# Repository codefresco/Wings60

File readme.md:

# Wings60

Wings60 is an open source split keyboard designed after trying many existing split layouts.

## Why this layout

This keyboard is different in:

- Improved key access for the thumb cluster, two 1.5u key with good access.
- Uses a natural thumb cluster orientation selected after testing many existing layouts.
- Uses the most popular column stagger.
- Keeps the same PCB usable for wired or wireless builds, including a power slide switch, JST PH2.0 battery plug, and between-halves interconnects on the PCB.
- Uses USB-C for wired interconnect between halves, it can be hot-plugged without damaging microcontrollers.
- Supports pro-micro pinout controllers such as Nice!Nano, Pro Micro ATmega32u4, and Pro Micro RP2040.
- Uses low-power RGB LEDs (SK6803 mini-e), which draw less power than common WS2812B and SK6812 variants.
- Includes a slide switch to cut LED power for zero LED idle current in power-conscious assemblies.
- Stays compact while keeping a top number row.

## How to assemble

> [!WARNING]
> If you use a 3V microcontroller (for example Nice!Nano or RP2040), do not plug a powered USB cable into the between-halves interconnect USB-C port. With a standard usb c cable and device, this would not be an issue bacause the CC pin on the interconnect is not connected. With a floating CC pin the device would not power the USB-C port. However, some USB-A to USB-C cables or devices do not comply with this standard and present 5v to the USB-C VBUS anyway, and this can damage the microcontroller. To make it mistake proof:
> - For nice! nano compatible and wireless builds print the case with interconect port covered
> - For wired builds with 3V microcontrollers do not connect he VCC pin on microcontroller to the pcb (don't pin if using mill max or similar pins, clip the pin if using ez solder, etc.) and bridge the VCC pin of the PCB to RAW using a short wire on back of the PCB

> [!WARNING]
> Before soldering switches, make sure the microcontroller USB connector is clearly accessible in your chosen case. After switches are soldered, the case top is sandwiched between switches and PCB, and changing the top case becomes difficult. If you want to be able to remove the PCB more easily, check the PCB-mount-switches case variant in [case](./case).

### Bill of materials

- See designs in [case](./case), pick one and print it. You can also design your own case around the [Case design outline](./case/design-outline), both dxf and svg are included.
- Sockets for MCU: one of EZ-Solder Machine Sockets or a 40-pin machined IC breakable female header strip with Mill-Max pins is recommended for a total socket height of 4.5-5mm. This works best with the 3D printable case designs in [case](./case). Check USB connector height after assembly against the case USB opening. If your USB sits higher/lower, use the adjustable USB case variant described in [case/readme.md](./case/readme.md). A good guide to socketing microcontrollers is available here: [Machine pin socket guide](https://github.com/joric/nrfmicro/wiki/Sockets#machine-pin-socket)
- Two pro micros: use any board with firmware already available in [firmware](./firmware), or any pro-micro-pinout compatible board and adjust firmware as needed. For wireless, use Nice!Nano or compatible SuperMini nRF52840.
- Either 4x 9-10mm standoffs with 4x M2x8 and 4x M2x4 screws for each half, or 4x M2x4 heat inserts with the heat-insert-compatible case bottom. See [case/readme.md](./case/readme.md).
- Non-slip rubber feet, 4x per half. 6mm diameter x 2mm height works well.
- [Wired only] A USB-C to USB-C cable for connecting the right and left halves.
- [Wireless only] A JST PH2.0 battery up to 5mm height. Check dimensions against the case if using the designs in [case](./case).
- Switches and keycaps.

### Wired build

1. Flash firmware using instructions here [firmware/readme.md](./firmware/readme.md)
2. Solder and socket the microcontrollers to PCBs, **face down**. USB side must face the PCB. A good socketing guide: [Splitkb microcontroller guide](https://docs.splitkb.com/product-guides/aurora-series/build-guide/microcontrollers)
3. Check USB height to make sure it fits the case designs in [case](./case). If it fits fixed-USB, use that variant; otherwise adjust USB height in the movable/adjustable variant in your slicer.
4. Fit switches to the case, minding pin orientation.

5. Fit the PCB to the case with flat side toward switches and components facing away from switches, so switch pins come out through the PCB. PCB should rest on the bottom of the switches. You may need gentle pressure for switch mounting pins to pop in.
6. Check no switch has popped out, and all switches are firmly seated on top of the case top side. Then solder all switch legs to the PCB.
7. If using standoff bottoms, screw each standoff to the case with M2x8 screws. V-shaped heads sit flush in the top-side recesses.
8. Screw case bottoms to standoffs using M2x4 screws, then apply non-slip feet.
9. If using heat-insert bottoms, install heat inserts and fit the bottom to the top using M4x8 screws.

The halves can now be connected using the USB-C cable. Connect one microcontroller to your PC (either half, but not both).

Use [Vial](https://get.vial.today/) to configure the keyboard. Configuration is saved to the half connected to the PC.

### Wireless build

TBD

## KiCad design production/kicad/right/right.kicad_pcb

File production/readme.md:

## Production Files

You can order this split keyboard from any major PCB manufacturer using the production-ready files in this directory.

- `left/` contains manufacturing files for the left PCB
- `right/` contains manufacturing files for the right PCB

## Example: Ordering from JLCPCB

1. Open JLCPCB and start a new PCB order.
2. Upload the left and right Gerber ZIPs separately (one order per side).
3. Confirm board specs (dimensions, thickness, copper weight, solder mask color, and finish).
4. Keep defaults unless you need specific changes.
5. Add both boards to cart, review, and place the order.

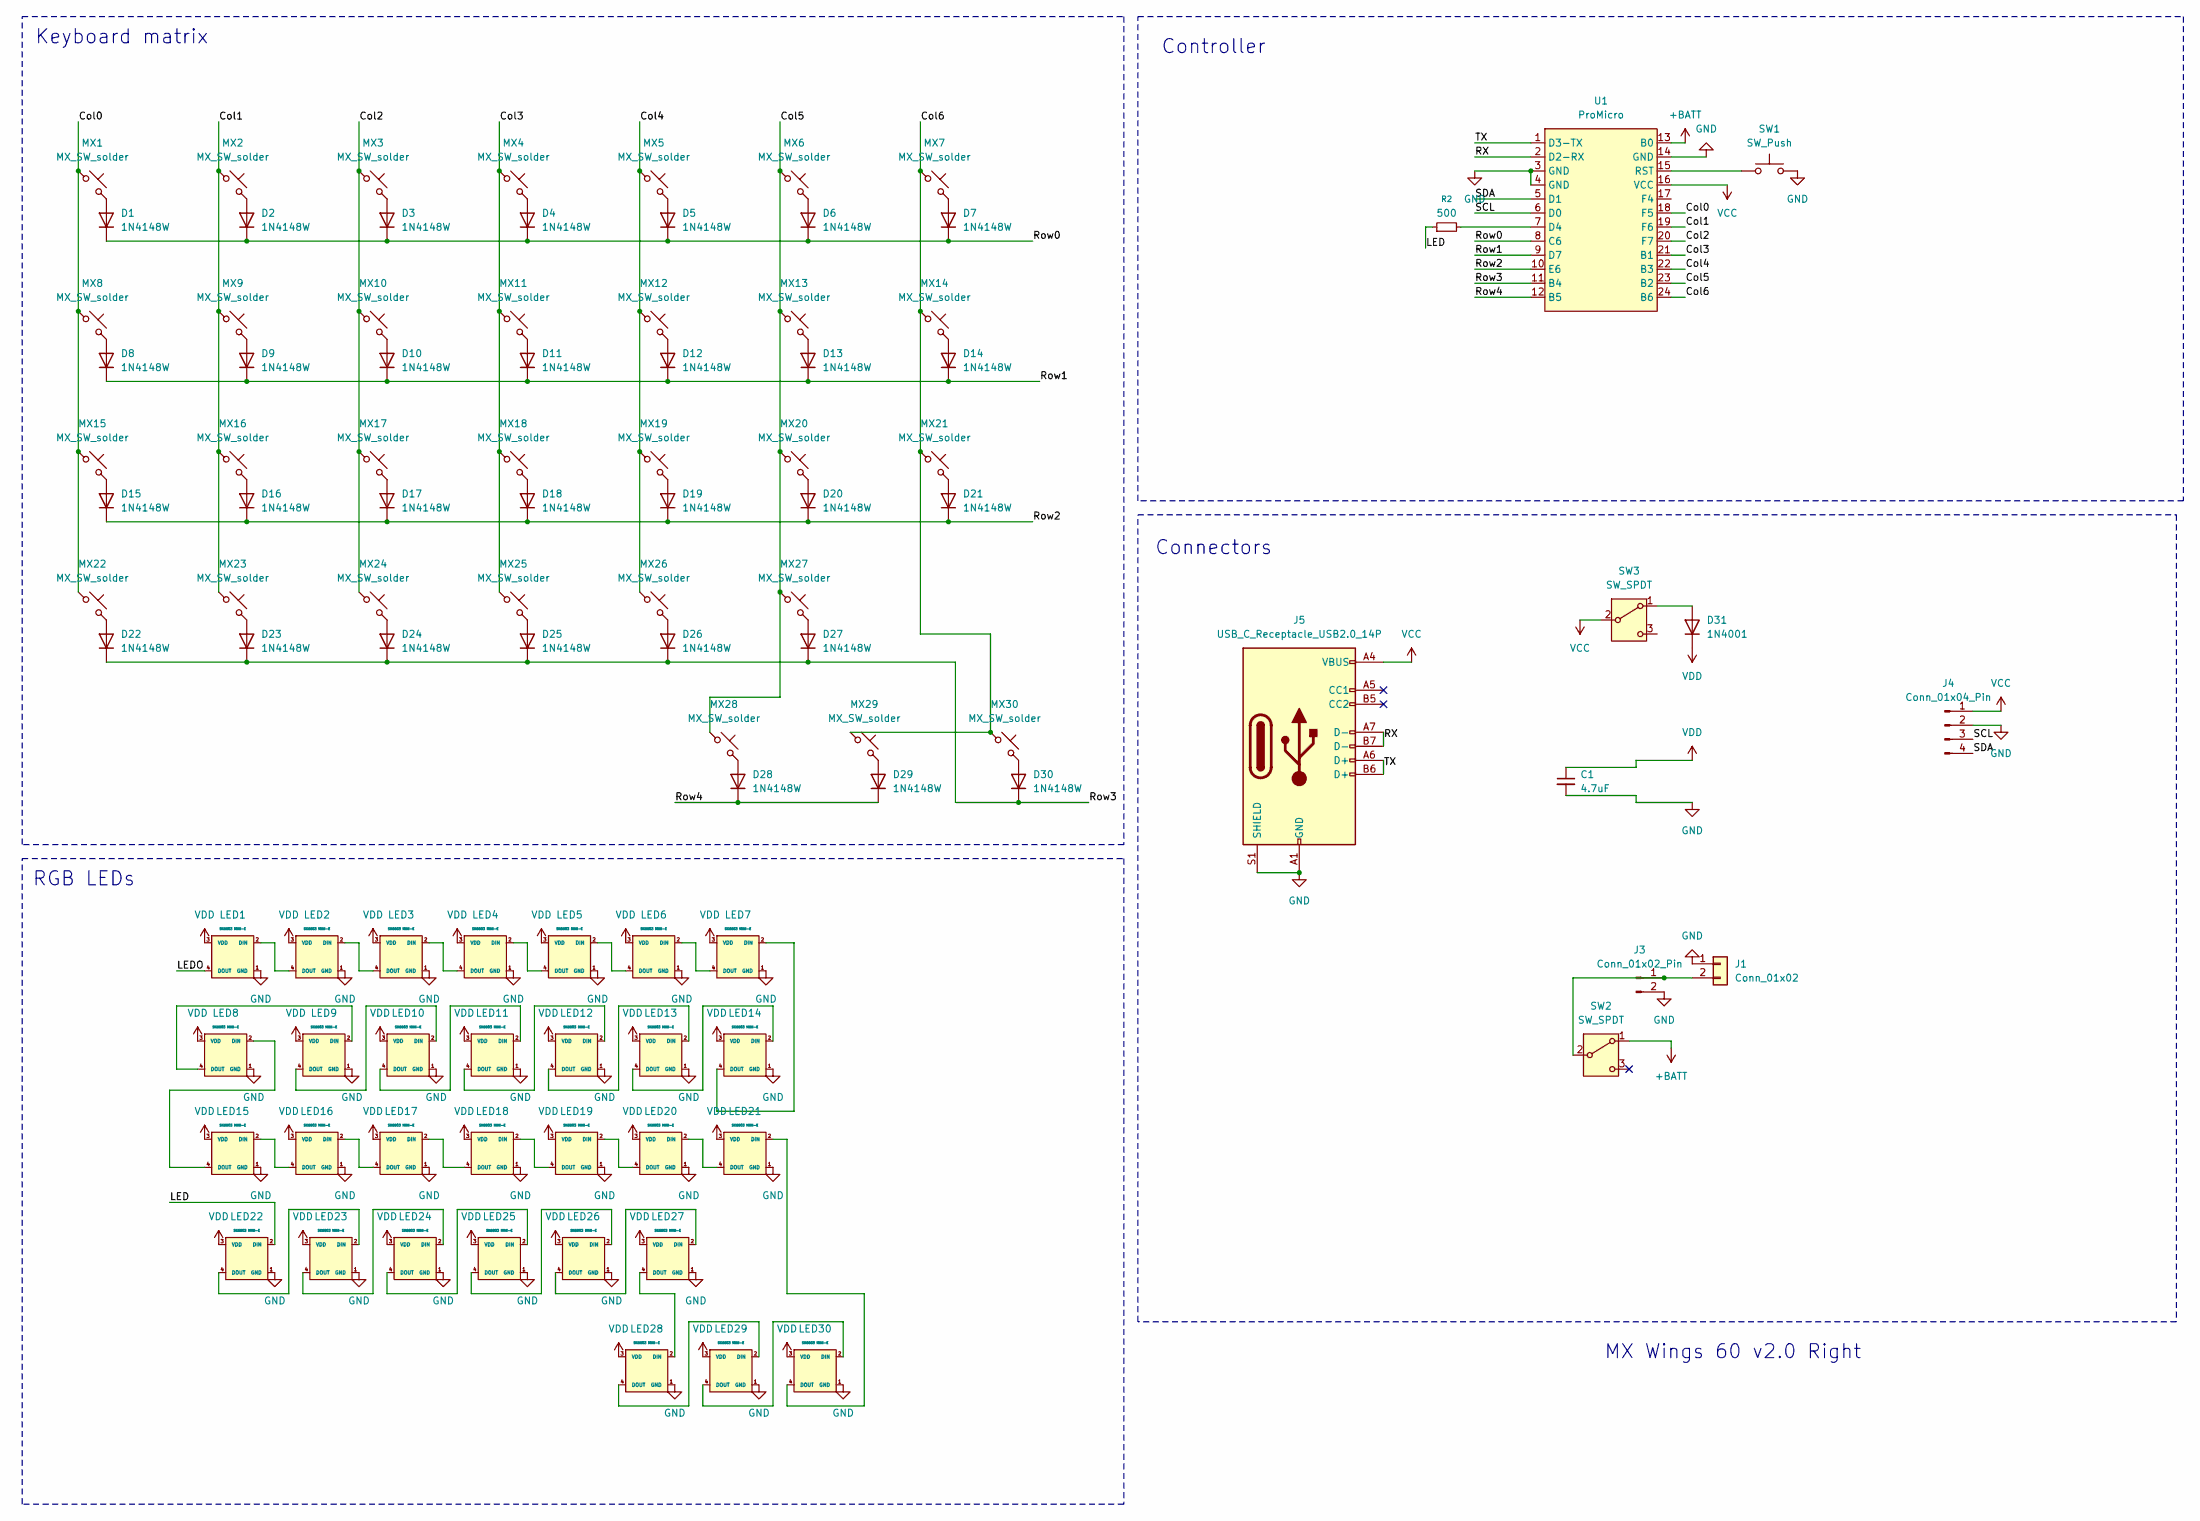
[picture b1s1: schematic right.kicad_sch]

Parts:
C1: 4.7uF; C_0603_1608Metric; LCSC C19666
D1, D2, D3, D4, D5, D6, D7, D8, D9, D10, D11, D12, D13, D14, D15, D16, D17, D18, D19, D20, D21, D22, D23, D24, D25, D26, D27, D28, D29, D30: 1N4148W; D_SOD-123
D31: 1N4001; D_SMA; LCSC C727079
J1: Conn_01x02; JST S2B-PH-SM4-TB-1x02-JST-PH
J3: Conn_01x02_Pin; PinHeader_1x02_P2.54mm_Vertical
J4: Conn_01x04_Pin; PinHeader_1x04_P2.54mm_Vertical
J5: USB_C_Receptacle_USB2.0_14P; USB_C_Receptacle_HRO_TYPE-C-31-M-12; LCSC C165948
LED1, LED2, LED3, LED4, LED5, LED6, LED7, LED8, LED9, LED10, LED11, LED12, LED13, LED14, LED15, LED16, LED17, LED18, LED19, LED20, LED21, LED22, LED23, LED24, LED25, LED26, LED27, LED28, LED29, LED30: SK6803 MINI-E; SK6803_MINI-E_v3.5.5_1; JLCPCB PN C5242955
MX1, MX2, MX3, MX4, MX5, MX6, MX7, MX8, MX9, MX10, MX11, MX12, MX13, MX14, MX15, MX16, MX17, MX18, MX19, MX20, MX21, MX22, MX23, MX24, MX25, MX26, MX27, MX28: MX_SW_solder; SW_MX_1u
MX29, MX30: MX_SW_solder; SW_MX_1.5u
R2: 500; R_0402_1005Metric; LCSC C20607727
SW1: SW_Push; SW_SPST_TL3342; LCSC C115351
SW2, SW3: SW_SPDT; SW_SPDT_Shouhan_MSK12C02
U1: ProMicro; ProMicro_USBdn

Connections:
+BATT: SW2.1 (A), U1.13 (B0)
/Col0: MX1.1, MX8.1, MX15.1, MX22.1, U1.18 (F5)
/Col1: MX2.1, MX9.1, MX16.1, MX23.1, U1.19 (F6)
/Col2: MX3.1, MX10.1, MX17.1, MX24.1, U1.20 (F7)
/Col3: MX4.1, MX11.1, MX18.1, MX25.1, U1.21 (B1)
/Col4: MX5.1, MX12.1, MX19.1, MX26.1, U1.22 (B3)
/Col5: MX6.1, MX13.1, MX20.1, MX27.1, MX28.1, U1.23 (B2)
/Col6: MX7.1, MX14.1, MX21.1, MX29.1, MX30.1, U1.24 (B6)
/LED: LED22.2 (DIN), R2.1
/LEDO: LED1.4 (DOUT)
/RX: J5.A7 (D-), J5.B7 (D-), U1.2 (D2-RX)
/Row0: D1.1 (K), D2.1 (K), D3.1 (K), D4.1 (K), D5.1 (K), D6.1 (K), D7.1 (K), U1.8 (C6)
/Row1: D8.1 (K), D9.1 (K), D10.1 (K), D11.1 (K), D12.1 (K), D13.1 (K), D14.1 (K), U1.9 (D7)
/Row2: D15.1 (K), D16.1 (K), D17.1 (K), D18.1 (K), D19.1 (K), D20.1 (K), D21.1 (K), U1.10 (E6)
/Row3: D22.1 (K), D23.1 (K), D24.1 (K), D25.1 (K), D26.1 (K), D27.1 (K), D30.1 (K), U1.11 (B4)
/Row4: D28.1 (K), D29.1 (K), U1.12 (B5)
/SCL: J4.3, U1.6 (D0)
/SDA: J4.4, U1.5 (D1)
/TX: J5.A6 (D+), J5.B6 (D+), U1.1 (D3-TX)
GND: C1.2, J1.1, J3.2, J4.2, J5.A1 (GND), J5.A12 (GND), J5.B1 (GND), J5.B12 (GND), J5.S1 (SHIELD), LED1.1 (GND), LED2.1 (GND), LED3.1 (GND), LED4.1 (GND), LED5.1 (GND), LED6.1 (GND), LED7.1 (GND), LED8.1 (GND), LED9.1 (GND), LED10.1 (GND), LED11.1 (GND), LED12.1 (GND), LED13.1 (GND), LED14.1 (GND), LED15.1 (GND), LED16.1 (GND), LED17.1 (GND), LED18.1 (GND), LED19.1 (GND), LED20.1 (GND), LED21.1 (GND), LED22.1 (GND), LED23.1 (GND), LED24.1 (GND), LED25.1 (GND), LED26.1 (GND), LED27.1 (GND), LED28.1 (GND), LED29.1 (GND), LED30.1 (GND), SW1.2, U1.3 (GND), U1.4 (GND), U1.14 (GND)
unnamed: D1.2 (A), MX1.2
unnamed: D2.2 (A), MX2.2
unnamed: D3.2 (A), MX3.2
unnamed: D4.2 (A), MX4.2
unnamed: D5.2 (A), MX5.2
unnamed: D6.2 (A), MX6.2
unnamed: D7.2 (A), MX7.2
unnamed: D8.2 (A), MX8.2
unnamed: D9.2 (A), MX9.2
unnamed: D10.2 (A), MX10.2
unnamed: D11.2 (A), MX11.2
unnamed: D12.2 (A), MX12.2
unnamed: D13.2 (A), MX13.2
unnamed: D14.2 (A), MX14.2
unnamed: D15.2 (A), MX15.2
unnamed: D16.2 (A), MX16.2
unnamed: D17.2 (A), MX17.2
unnamed: D18.2 (A), MX18.2
unnamed: D19.2 (A), MX19.2
unnamed: D20.2 (A), MX20.2
unnamed: D21.2 (A), MX21.2
unnamed: D22.2 (A), MX22.2
unnamed: D23.2 (A), MX23.2
unnamed: D24.2 (A), MX24.2
unnamed: D25.2 (A), MX25.2
unnamed: D26.2 (A), MX26.2
unnamed: D27.2 (A), MX27.2
unnamed: D28.2 (A), MX28.2
unnamed: D29.2 (A), MX29.2
unnamed: D30.2 (A), MX30.2
unnamed: D31.2 (A), SW3.1 (A)
unnamed: J1.2, J3.1, SW2.2 (B)
unnamed: LED1.2 (DIN), LED2.4 (DOUT)
unnamed: LED2.2 (DIN), LED3.4 (DOUT)
unnamed: LED3.2 (DIN), LED4.4 (DOUT)
unnamed: LED4.2 (DIN), LED5.4 (DOUT)
unnamed: LED5.2 (DIN), LED6.4 (DOUT)
unnamed: LED6.2 (DIN), LED7.4 (DOUT)
unnamed: LED8.4 (DOUT), LED9.2 (DIN)
unnamed: LED9.4 (DOUT), LED10.2 (DIN)
unnamed: LED10.4 (DOUT), LED11.2 (DIN)
unnamed: LED11.4 (DOUT), LED12.2 (DIN)
unnamed: LED12.4 (DOUT), LED13.2 (DIN)
unnamed: LED13.4 (DOUT), LED14.2 (DIN)
unnamed: LED7.2 (DIN), LED14.4 (DOUT)
unnamed: LED15.2 (DIN), LED16.4 (DOUT)
unnamed: LED8.2 (DIN), LED15.4 (DOUT)
unnamed: LED16.2 (DIN), LED17.4 (DOUT)
unnamed: LED17.2 (DIN), LED18.4 (DOUT)
unnamed: LED18.2 (DIN), LED19.4 (DOUT)
unnamed: LED19.2 (DIN), LED20.4 (DOUT)
unnamed: LED20.2 (DIN), LED21.4 (DOUT)
unnamed: LED21.2 (DIN), LED30.4 (DOUT)
unnamed: LED22.4 (DOUT), LED23.2 (DIN)
unnamed: LED23.4 (DOUT), LED24.2 (DIN)
unnamed: LED24.4 (DOUT), LED25.2 (DIN)
unnamed: LED25.4 (DOUT), LED26.2 (DIN)
unnamed: LED26.4 (DOUT), LED27.2 (DIN)
unnamed: LED27.4 (DOUT), LED28.2 (DIN)
unnamed: LED28.4 (DOUT), LED29.2 (DIN)
unnamed: LED29.4 (DOUT), LED30.2 (DIN)
unnamed: R2.2, U1.7 (D4)
unnamed: SW1.1, U1.15 (RST)
VCC: J4.1, J5.A4 (VBUS), J5.A9 (VBUS), J5.B4 (VBUS), J5.B9 (VBUS), SW3.2 (B), U1.16 (VCC)
VDD: C1.1, D31.1 (K), LED1.3 (VDD), LED2.3 (VDD), LED3.3 (VDD), LED4.3 (VDD), LED5.3 (VDD), LED6.3 (VDD), LED7.3 (VDD), LED8.3 (VDD), LED9.3 (VDD), LED10.3 (VDD), LED11.3 (VDD), LED12.3 (VDD), LED13.3 (VDD), LED14.3 (VDD), LED15.3 (VDD), LED16.3 (VDD), LED17.3 (VDD), LED18.3 (VDD), LED19.3 (VDD), LED20.3 (VDD), LED21.3 (VDD), LED22.3 (VDD), LED23.3 (VDD), LED24.3 (VDD), LED25.3 (VDD), LED26.3 (VDD), LED27.3 (VDD), LED28.3 (VDD), LED29.3 (VDD), LED30.3 (VDD)

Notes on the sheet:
Connectors
MX Wings 60 v2.0 Right
Controller
RGB LEDs
Keyboard matrix

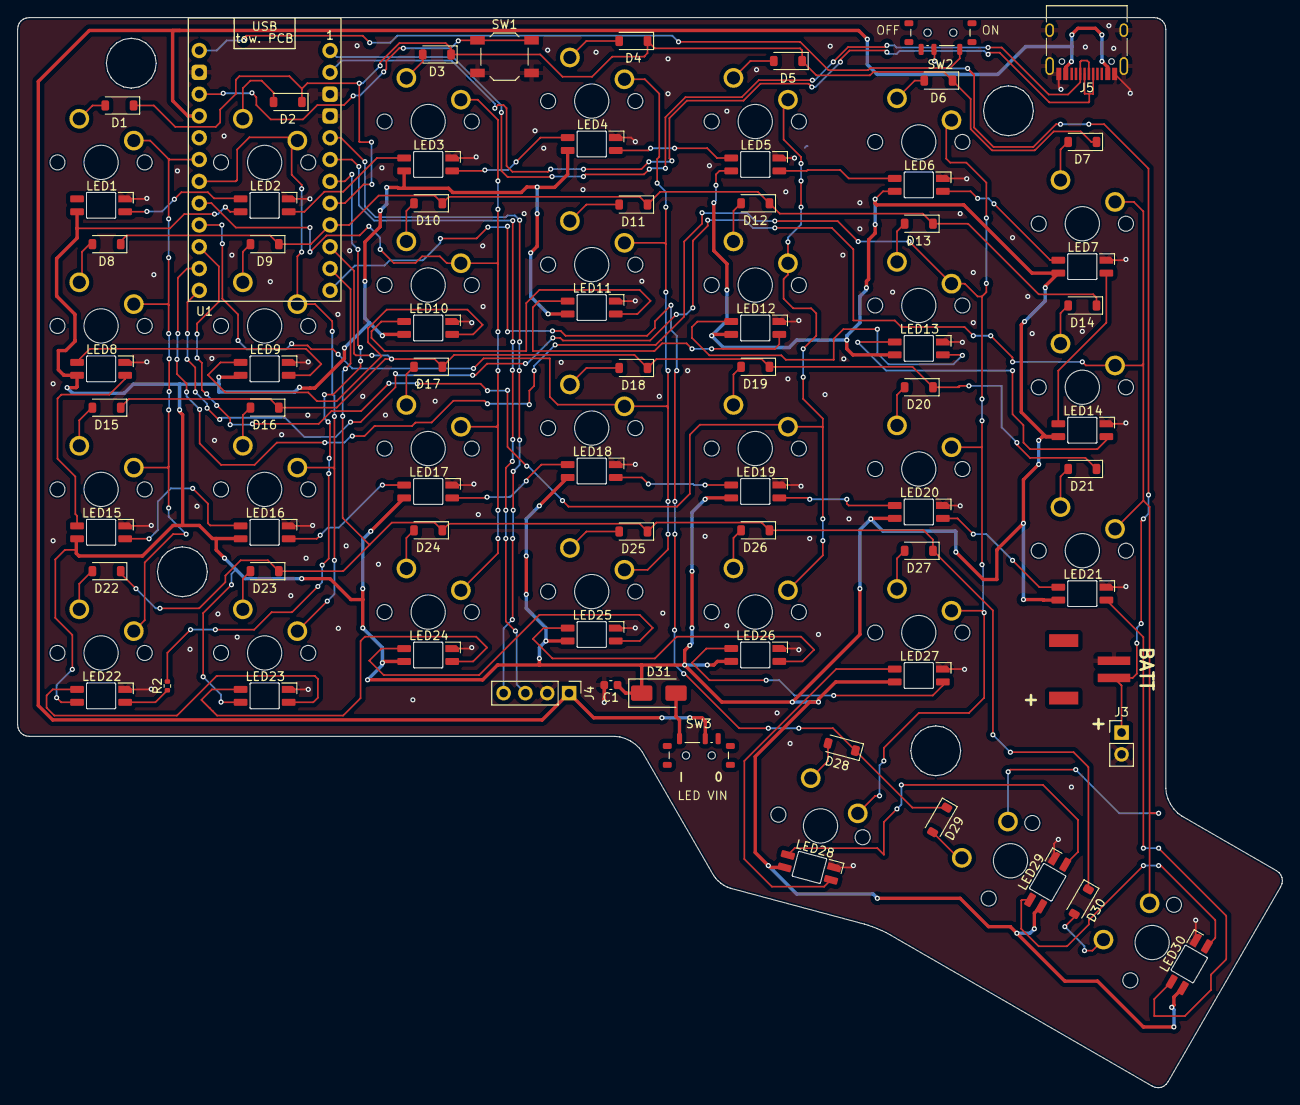
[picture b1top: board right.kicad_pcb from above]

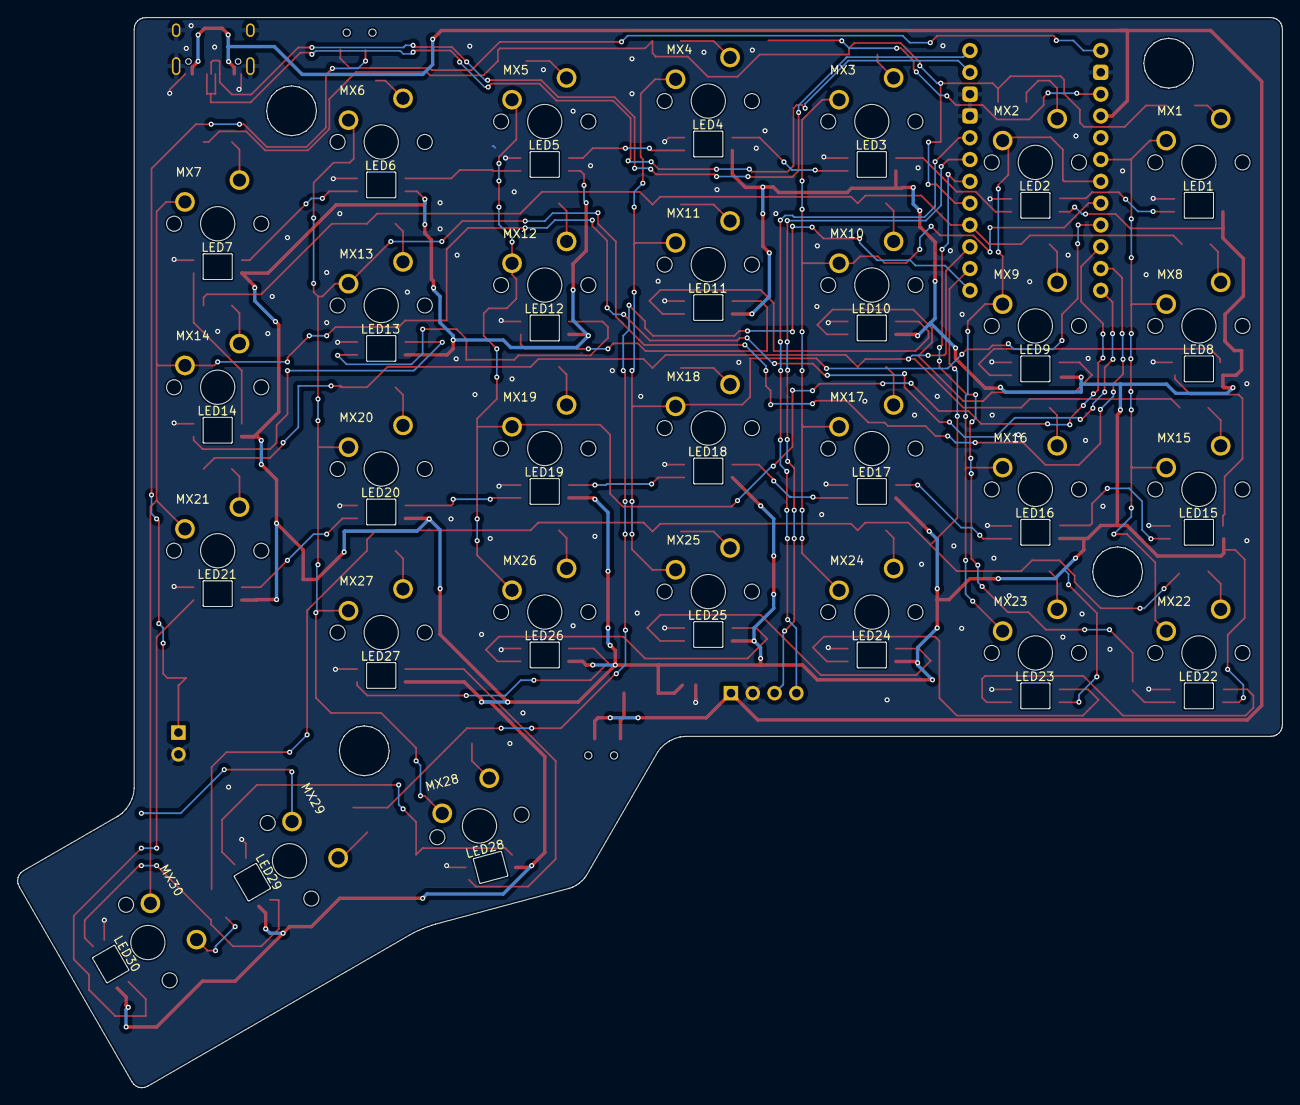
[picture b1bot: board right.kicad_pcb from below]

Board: 2 copper layers, 147.3 x 124.7 mm, 101 parts (30 on the bottom side), 84 nets.

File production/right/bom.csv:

Designator,Footprint,Quantity,Value,LCSC Part #
C1,Capacitor_0603,1,4.7uF,C19666
"D1, D10, D11, D12, D13, D14, D15, D16, D17, D18, D19, D2, D20, D21, D22, D23, D24, D25, D26, D27, D28, D29, D3, D30, D4, D5, D6, D7, D8, D9",D_SOD-123,30,1N4148W,
D31,D_SMA,1,1N4001,C727079
J1,Connector_1x02_JST-PH,1,Conn_01x02,C295747
J3,PinHeader_1x02_P2.54mm_Vertical,1,Conn_01x02_Pin,
J5,USB_C_Receptacle_HRO_TYPE-C-31-M-12,1,USB_C_Receptacle_USB2.0_14P,C165948
"LED1, LED10, LED11, LED12, LED13, LED14, LED15, LED16, LED17, LED18, LED19, LED2, LED20, LED21, LED22, LED23, LED24, LED25, LED26, LED27, LED28, LED29, LED3, LED30, LED4, LED5, LED6, LED7, LED8, LED9",SK6803_MINI-E_v3.5.5_1,30,SK6803 MINI-E,C5242955
R2,Resistor_0402,1,500,C20607727
SW1,SW_SPST_TL3342,1,SW_Push,C115351
"SW2, SW3",SW_SPDT_Shouhan_MSK12C02,2,SW_SPDT,C963206

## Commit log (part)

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2026-04-07 Initial right half preview
2026-04-12 Updated MCU position for full compatibility, added switch for led power line
2026-04-23 Wings60 v2 firmware
2026-04-23 Fixed right column order for avr. Added readme for firmware.
2026-04-23 Rename Wings60V2 to Wings60 in readme
2026-04-23 Updated firmware readme
2026-04-25 Added case
2026-04-25 Added firmware readme
2026-04-25 Added production files and readme
2026-04-25 Update readme with flashing instructions for firmware
    Added instructions for flashing compiled firmware variants.
2026-04-25 Added firmware flashing instruction to readme
2026-04-25 Added design outline svg and dxf
2026-04-26 Added case for pcb mounting switches
2026-05-12 Update readme with refined keyboard layout description
    Refined the description of the Wings60 keyboard layout, emphasizing its unique features and improvements over common layouts.
2026-05-16 Added firmware for RP2040
2026-05-16 Added case type for mcus with inset usb port
2026-05-16 Updated case readme
2026-05-17 Improved case design for pcb mount switches
2026-05-17 Improved pcb mount case top and updated case readme
2026-05-17 Updated main and case readme
2026-05-18 Added warnings to main readme
2026-05-18 Fixed sample images in case readme, linked to design outline in main readme
2026-05-20 Enhance assembly instructions with safety warnings
    Added additional warnings for 3V microcontroller usage to prevent damage and improve assembly instructions.
2026-06-03 Through hole 4 row choc prototype
2026-06-08 Wing46 prototype
2026-06-25 Wireless dongle pcb
2026-06-27 Added kicad files
